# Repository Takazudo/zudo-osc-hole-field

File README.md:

# zudo-osc-hole-field

A standalone, cable-patched analog synthesizer on one flat 318 × 298 mm front panel, with 180 jacks above 144 controls and 33 module instances. Documentation domain: [zudo-osc-hole-field.zudolab.dev](https://zudo-osc-hole-field.zudolab.dev).

**Status:** pre-release design; no fabrication release exists.

The site is built with [zudo-circuit-doc](https://github.com/Takazudo/zudo-circuit-doc) on top of [zudo-doc](https://github.com/zudolab/zudo-doc). Authored project documentation lives under `doc/src/content/docs/`; exact-component evidence lives under `.claude/skills/`, and the component pages are generated from that evidence.

GitHub Actions runs the evidence validation, documentation checks, site build and built-site checks, plus Python unit tests under `scripts/` and `design/`, for pull requests and pushes to `main`. CI also replays aggregate source regeneration, including pinned native schematic and display checks, and retains any generated diff when that replay fails. These checks need no secrets and do not deploy the site; they do not establish electrical or physical qualification.

## Commands

| Command | What it does |
| --- | --- |
| `pnpm install` | Install dependencies |
| `pnpm dev` | Dev server, regenerating component pages as evidence changes |
| `pnpm build` | Publish selected models, generate component pages, build the site |
| `pnpm check` | Validate evidence, check generated output is current, type-check the site |
| `pnpm check:site` | Post-build checks: references, publication scope, links |
| `pnpm circuit:check` | Validate the component evidence (offline) |
| `pnpm circuit:generate` | Regenerate the component pages and the preflight report |
| `pnpm circuit:doctor` | Report required and optional tools |
| `pnpm previews:generate` | Render footprint previews (optional; needs Docker) |

Agent-facing commands (new component bundles, online source refresh) are listed in [circuit/WORKFLOW.md](circuit/WORKFLOW.md).

## Tool requirements

| Tool | Required | Used for |
| --- | --- | --- |
| Node.js 24 LTS (`>=24 <25`) | Yes | Everything |
| pnpm 11 (via corepack) | Yes | Install and scripts |
| Python ≥3.10 | Yes | Evidence validation (standard library only) |
| git | Yes | History and review diffs |
| Docker with the pinned KiCad image | No | Footprint previews |
| Chrome | No | Browser smoke check |
| Network | No | Downloading sources and assets only; the build is offline |
| easyeda2kicad | No | Importing CAD assets for LCSC-listed parts |

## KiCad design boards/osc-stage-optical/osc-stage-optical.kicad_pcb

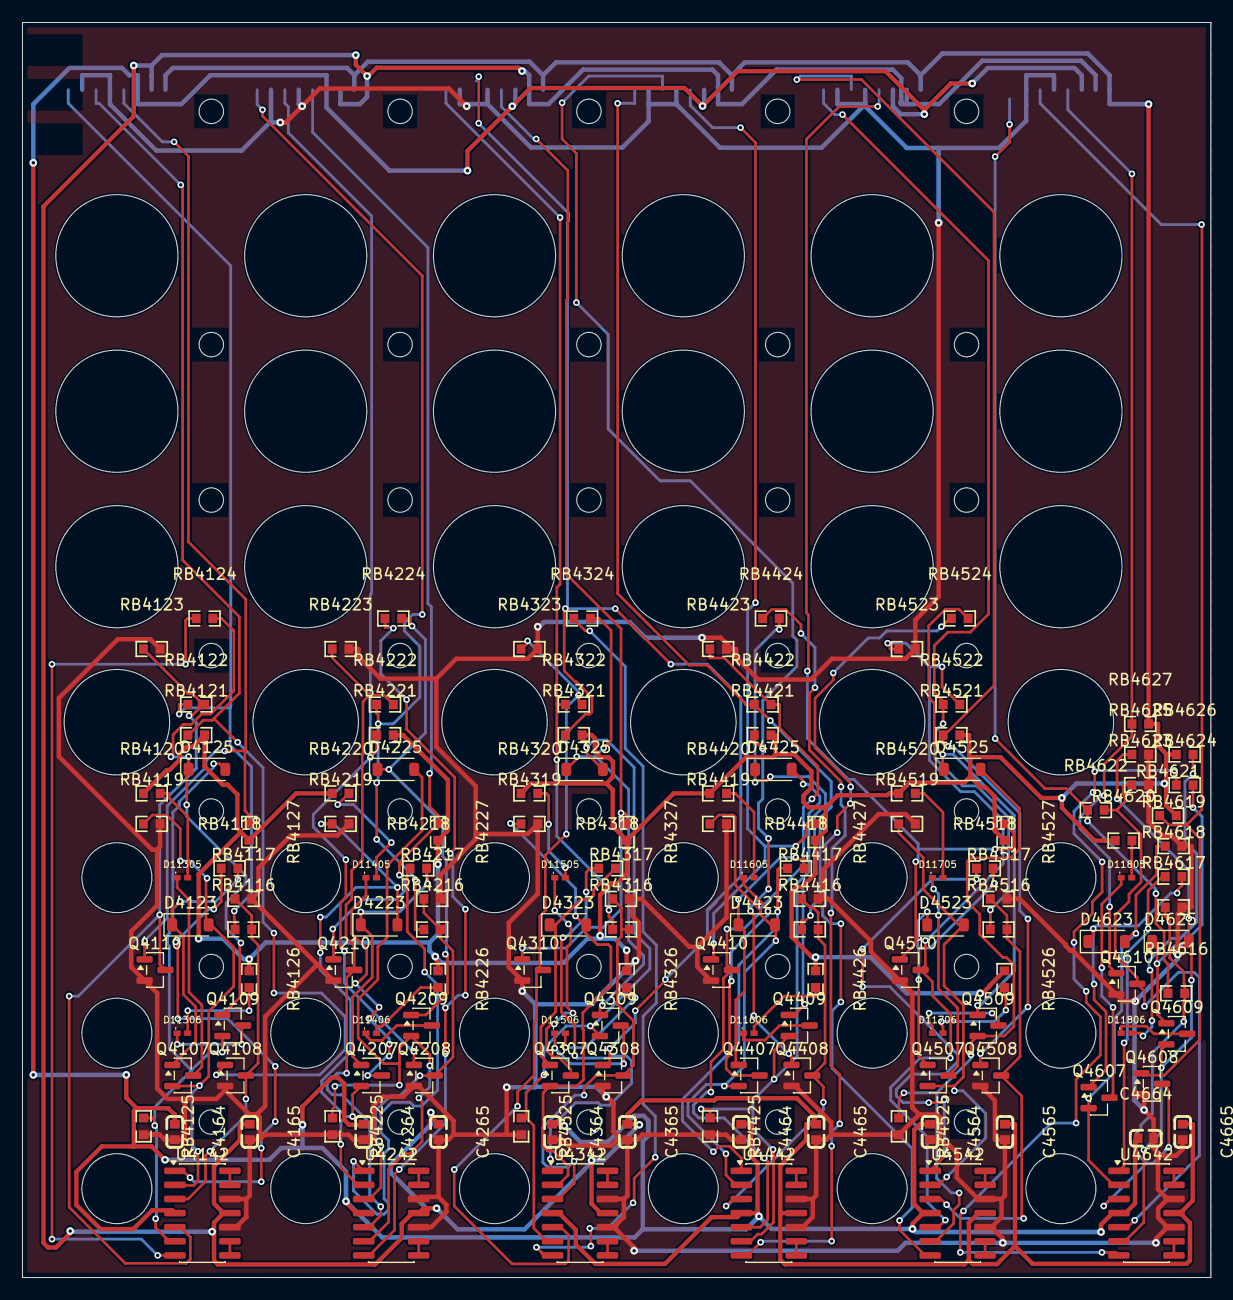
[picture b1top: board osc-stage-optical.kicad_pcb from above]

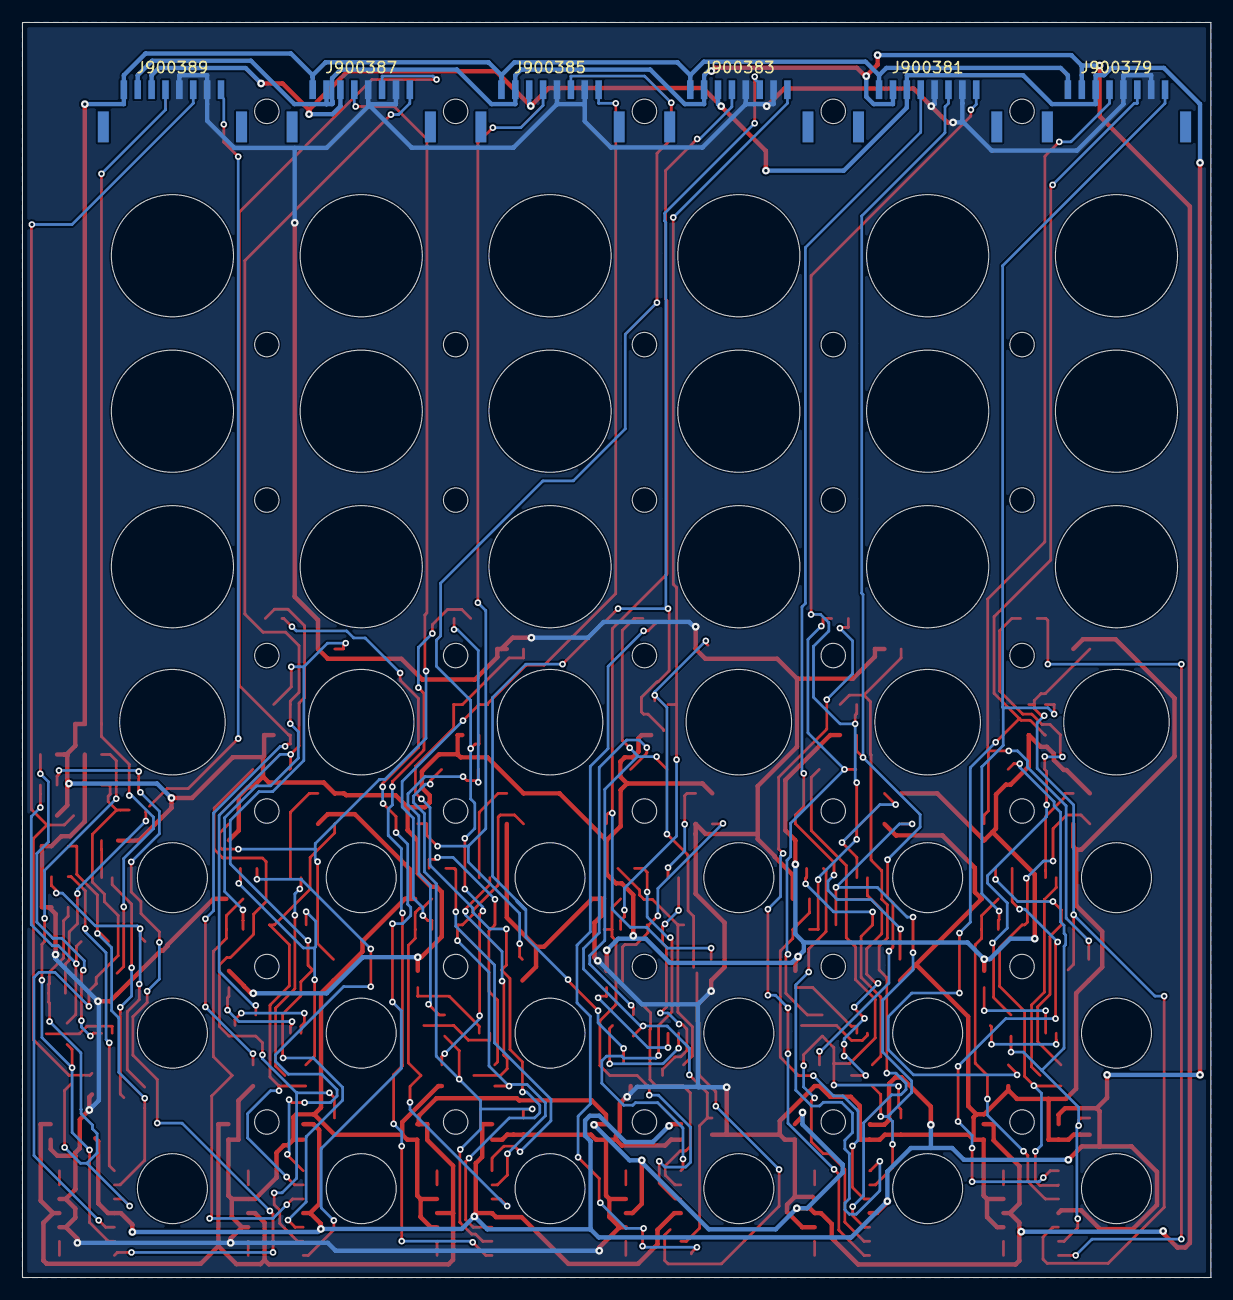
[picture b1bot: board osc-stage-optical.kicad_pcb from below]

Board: 2 copper layers, 107.0 x 113.0 mm, 221 parts (6 on the bottom side), 106 nets.

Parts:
C4164, C4165, C4264, C4265, C4364, C4365, C4464, C4465, C4564, C4565, C4664, C4665: 100 nF; C0603
D4123, D4125, D4223, D4225, D4323, D4325, D4423, D4425, D4523, D4525, D4623, D4625: BAS16GW-QX; SOD-123
D11305, D11306, D11405, D11406, D11505, D11506, D11605, D11606, D11705, D11706, D11805, D11806: APHHS1005QWF/D; LED0402-Kingbright-White
J900379, J900381, J900383, J900385, J900387, J900389: BM08B-GHS-TBT(LF)(SN); JST_GH8_BM_TopEntry
MH_EL-OPT-1, MH_EL-OPT-2, MH_EL-OPT-3, MH_EL-OPT-4, MH_EL-OPT-5, MH_EL-OPT-6, MH_EL-OPT-7, MH_EL-OPT-8, MH_EL-OPT-9, MH_EL-OPT-10, MH_EL-OPT-11, MH_EL-OPT-12, MH_EL-OPT-13, MH_EL-OPT-14, MH_EL-OPT-15, MH_EL-OPT-16, MH_EL-OPT-17, MH_EL-OPT-18, MH_EL-OPT-19, MH_EL-OPT-20, MH_EL-OPT-21, MH_EL-OPT-22, MH_EL-OPT-23, MH_EL-OPT-24, MH_EL-OPT-25, MH_EL-OPT-26, MH_EL-OPT-27, MH_EL-OPT-28, MH_EL-OPT-29, MH_EL-OPT-30, MH_EL-OPT-31, MH_EL-OPT-32, MH_EL-OPT-33, MH_EL-OPT-34, MH_EL-OPT-35: NPTH mounting hole
MH_EL-PASSAGE-1, MH_EL-PASSAGE-2, MH_EL-PASSAGE-3, MH_EL-PASSAGE-4, MH_EL-PASSAGE-5, MH_EL-PASSAGE-6, MH_EL-PASSAGE-7, MH_EL-PASSAGE-8, MH_EL-PASSAGE-9, MH_EL-PASSAGE-10, MH_EL-PASSAGE-11, MH_EL-PASSAGE-12, MH_EL-PASSAGE-13, MH_EL-PASSAGE-14, MH_EL-PASSAGE-15, MH_EL-PASSAGE-16, MH_EL-PASSAGE-17, MH_EL-PASSAGE-18, MH_EL-PASSAGE-19, MH_EL-PASSAGE-20, MH_EL-PASSAGE-21, MH_EL-PASSAGE-22, MH_EL-PASSAGE-23, MH_EL-PASSAGE-24, MH_EL-PASSAGE-25, MH_EL-PASSAGE-26, MH_EL-PASSAGE-27, MH_EL-PASSAGE-28, MH_EL-PASSAGE-29, MH_EL-PASSAGE-30, MH_EL-PASSAGE-31, MH_EL-PASSAGE-32, MH_EL-PASSAGE-33, MH_EL-PASSAGE-34, MH_EL-PASSAGE-35, MH_EL-PASSAGE-36, MH_EL-PASSAGE-37, MH_EL-PASSAGE-38, MH_EL-PASSAGE-39, MH_EL-PASSAGE-40, MH_EL-PASSAGE-41, MH_EL-PASSAGE-42: NPTH mounting hole
Q4107, Q4109, Q4207, Q4209, Q4307, Q4309, Q4407, Q4409, Q4507, Q4509, Q4607, Q4609: MMBT3904,215; SOT-23
Q4108, Q4110, Q4208, Q4210, Q4308, Q4310, Q4408, Q4410, Q4508, Q4510, Q4608, Q4610: 2N7002,215; SOT-23
RB4116, RB4122, RB4216, RB4222, RB4316, RB4322, RB4416, RB4422, RB4516, RB4522, RB4616, RB4622: 150000 Ω; R0603
RB4117, RB4118, RB4123, RB4124, RB4217, RB4218, RB4223, RB4224, RB4317, RB4318, RB4323, RB4324, RB4417, RB4418, RB4423, RB4424, RB4517, RB4518, RB4523, RB4524, RB4617, RB4618, RB4623, RB4624: 10000 Ω; R0603
RB4119, RB4125, RB4219, RB4225, RB4319, RB4325, RB4419, RB4425, RB4519, RB4525, RB4619, RB4625: 1000 Ω; R0603
RB4120, RB4126, RB4220, RB4226, RB4320, RB4326, RB4420, RB4426, RB4520, RB4526, RB4620, RB4626: 1200 Ω; R0603
RB4121, RB4127, RB4221, RB4227, RB4321, RB4327, RB4421, RB4427, RB4521, RB4527, RB4621, RB4627: 100000 Ω; R0603
U4142, U4242, U4342, U4442, U4542, U4642: OPA4196IDR; SOIC-14_3.9x8.7mm_P1.27mm

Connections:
+5V: J900379.8, J900381.8, J900383.8, J900385.8, J900387.8, J900389.8, RB4120.1, RB4121.2, RB4126.1, RB4127.2, RB4220.1, RB4221.2, RB4226.1, RB4227.2, RB4320.1, RB4321.2, RB4326.1, RB4327.2, RB4420.1, RB4421.2, RB4426.1, RB4427.2, RB4520.1, RB4521.2, RB4526.1, RB4527.2, RB4620.1, RB4621.2, RB4626.1, RB4627.2
+12V: C4164.1, C4264.1, C4364.1, C4464.1, C4564.1, C4664.1, J900379.6, J900381.6, J900383.6, J900385.6, J900387.6, J900389.6, U4142.4, U4242.4, U4342.4, U4442.4, U4542.4, U4642.4
-12V: C4165.1, C4265.1, C4365.1, C4465.1, C4565.1, C4665.1, J900379.7, J900381.7, J900383.7, J900385.7, J900387.7, J900389.7, U4142.11, U4242.11, U4342.11, U4442.11, U4542.11, U4642.11
AGND: C4164.2, C4165.2, C4264.2, C4265.2, C4364.2, C4365.2, C4464.2, C4465.2, C4564.2, C4565.2, C4664.2, C4665.2, J900379.2, J900379.4, J900381.2, J900381.4, J900383.2, J900383.4, J900385.2, J900385.4, J900387.2, J900387.4, J900389.2, J900389.4, Q4108.2, Q4110.2, Q4208.2, Q4210.2, Q4308.2, Q4310.2, Q4408.2, Q4410.2, Q4508.2, Q4510.2, Q4608.2, Q4610.2, RB4117.2, RB4119.2, RB4123.2, RB4125.2, RB4217.2, RB4219.2, RB4223.2, RB4225.2, RB4317.2, RB4319.2, RB4323.2, RB4325.2, RB4417.2, RB4419.2, RB4423.2, RB4425.2, RB4517.2, RB4519.2, RB4523.2, RB4525.2, RB4617.2, RB4619.2, RB4623.2, RB4625.2, U4142.10, U4142.12, U4242.10, U4242.12, U4342.10, U4342.12, U4442.10, U4442.12, U4542.10, U4542.12, U4642.10, U4642.12
X00BF5622D64D21A15AC7: J900389.3, Q4608.1, RB4621.1
X1AC60263070127D75110: D4225.1, Q4209.1, RB4224.2
X1BBA3C5B996B98DC88F4: J900383.5, Q4310.1, RB4327.1
X1D82190ED747CF04DE0E: RB4624.1, U4642.7
X1DC1CF348CA9F3663A68: Q4410.3, RB4422.2, RB4423.1, U4442.5
X1E1A841AE6BDBA6F12FD: D4423.1, Q4407.1, RB4418.2
X1E3069D9C725A8540F2B: Q4210.3, RB4222.2, RB4223.1, U4242.5
X1FFAABFEE1FB66BF068E: D4325.2, Q4309.2, RB4325.1, U4342.6
X2AC9B8A8C44204D4DCFE: D4423.2, Q4407.2, RB4419.1, U4442.2
X2E5349539AD45B40EC09: D4125.1, Q4109.1, RB4124.2
X4B6E43806072E34C24A9: D11505.2, RB4320.2
X5EF5AA803DEECA814BD8: D11605.2, RB4420.2
X6A8CD0115BB6A0D0366E: D11706.1, Q4509.3
X6A51B6341523E19D8CF4: D11806.1, Q4609.3
X6B20A2AEE7A32617CD3E: D11405.1, Q4207.3
X6C1DA0497CB43057E117: Q4608.3, RB4616.2, RB4617.1, U4642.3
X6E9F88B4B3BE457C0226: U4342.13, U4342.14
X7E65864BB7CF7411DC10: U4442.13, U4442.14
X8A939B676B6F87E5F9A3: J900383.1, RB4316.1, RB4322.1
X8ECADF7A8E0F09B77152: D11305.2, RB4120.2
X9A280F085D66F529A415: D11706.2, RB4526.2
X9B81034A8BEE6B2EBDA4: J900385.3, Q4408.1, RB4421.1
X9C2EA2BC9623A3E6139C: D11606.2, RB4426.2
X9E4D82CA4412C9189909: Q4508.3, RB4516.2, RB4517.1, U4542.3
X9E76C286BAE34857728C: D4323.2, Q4307.2, RB4319.1, U4342.2
X9F3B44E9C4F1B46F49CF: RB4124.1, U4142.7
X9F61A7055EEEA35F62E7: J900389.1, RB4616.1, RB4622.1
X10C845ED7B7C5BB89B7C: RB4224.1, U4242.7
X47BB1FB0495EA911FAB2: D4325.1, Q4309.1, RB4324.2
X61E1C31F3ACE5341D7D3: Q4408.3, RB4416.2, RB4417.1, U4442.3
X71B9E05195347FA9C8C2: J900387.1, RB4516.1, RB4522.1
X87EB8972925CDC4B1D2E: J900381.3, Q4208.1, RB4221.1
X88DA5861B6BCC3B653DE: D11606.1, Q4409.3
X95E38523BB35DF833AE9: J900385.1, RB4416.1, RB4422.1
X131A163062BE66F69054: J900385.5, Q4410.1, RB4427.1
X244B291CBC2C7076AA07: D11605.1, Q4407.3
X419B40DA0975D322AD5F: D11405.2, RB4220.2
X498F1E66A5FADE06B7E4: Q4308.3, RB4316.2, RB4317.1, U4342.3
X688ECBAA39258DC2D00D: D11805.2, RB4620.2
X789C67863FBCE430DA0E: RB4518.1, U4542.1
X799DB867A3031F5AB77F: RB4618.1, U4642.1
X853F40255E51475DF7A1: D4523.2, Q4507.2, RB4519.1, U4542.2
X867ABDC689D5BFF10061: Q4110.3, RB4122.2, RB4123.1, U4142.5
X2504E7ECC0354FA168E7: D4223.2, Q4207.2, RB4219.1, U4242.2
X3295DB827CE8AAE574FD: RB4324.1, U4342.7
X3439E778D35CDF6DFDF1: Q4108.3, RB4116.2, RB4117.1, U4142.3
X04963B7F211123194254: RB4318.1, U4342.1
X7307E027BF83453C3524: D11705.2, RB4520.2
X9141FD25BB2109174A88: U4442.8, U4442.9
X9858BBCA9970C9FCB86B: RB4524.1, U4542.7
X10852B4E217E1D395843: J900381.1, RB4216.1, RB4222.1
X25962DC0D080647130A4: U4542.13, U4542.14
X43904EB1FC7EDB0AA335: D11406.2, RB4226.2
X61003EE13806AD930803: J900387.5, Q4510.1, RB4527.1
X63613ECE89F282A509B6: J900383.3, Q4308.1, RB4321.1
X138812A99E0187B8D67A: D4625.2, Q4609.2, RB4625.1, U4642.6
X332730C2FDDA08CAED83: D4125.2, Q4109.2, RB4125.1, U4142.6
X634047C9CD5843892462: U4342.8, U4342.9
X4422711AFCCDBA718D4A: D4525.1, Q4509.1, RB4524.2
X53746081A37DAC301ADD: D11705.1, Q4507.3
X797009172D71EAFEBB1A: U4142.13, U4142.14
XA9DE434B9AA0F8C536DE: D11406.1, Q4209.3
XA68EA9E2F5379B7D8F08: D11305.1, Q4107.3
XAA0301884F69AD0E7337: J900379.5, Q4110.1, RB4127.1
XADBE90B291D159BD3BB1: D4523.1, Q4507.1, RB4518.2
XB2EBA66DAA21CB8551C8: RB4424.1, U4442.7
XB3B9A2AF2F7FA0D340E0: U4642.8, U4642.9
XB7B603420FD77620332F: D4425.1, Q4409.1, RB4424.2
XB7C2F315B2A72C7196F7: J900379.1, RB4116.1, RB4122.1
XB8D83C764066FEA571D7: J900381.5, Q4210.1, RB4227.1
XB9F0BC4557B5B5EF0AEC: Q4310.3, RB4322.2, RB4323.1, U4342.5
XB9FF60B0A66F70D425BE: D11805.1, Q4607.3
XB42EEE9219CFC7A853BD: D4323.1, Q4307.1, RB4318.2
XB899437C2EA9066F92F1: D4623.1, Q4607.1, RB4618.2
XBE667D2100526CFBC980: Q4510.3, RB4522.2, RB4523.1, U4542.5
XBED0A5748F4252A15663: D11306.2, RB4126.2
XC63C4BF13BA35D8AB361: D11806.2, RB4626.2
XCBB338FD60809F1C4554: U4242.13, U4242.14
XCF0902D8596AED7F7C86: D11505.1, Q4307.3
XCF44320172AB28A8C69A: U4642.13, U4642.14
XD5D1FFC8551A1CE41366: RB4418.1, U4442.1
XDCA4AB4D7D77D8669D15: Q4610.3, RB4622.2, RB4623.1, U4642.5
XDFCEC6E90F901E5E001F: D11506.2, RB4326.2
XE0FCBC3BB1F0803DF2AA: RB4218.1, U4242.1
XE1BE3DF4F60D2EE008D3: U4242.8, U4242.9
XE56B22348305C8B48C30: D4225.2, Q4209.2, RB4225.1, U4242.6
XE88A58D060DEC4E258C1: D4623.2, Q4607.2, RB4619.1, U4642.2
XE5206E58490CA0C0DF9B: D11506.1, Q4309.3
XE81531DE199582BE1344: J900389.5, Q4610.1, RB4627.1
XE1168244D1DE58C973DA: J900387.3, Q4508.1, RB4521.1
XEBD613C7EBC4FC656B12: D4223.1, Q4207.1, RB4218.2
XEE002239713F1E6CFAB6: D4123.1, Q4107.1, RB4118.2
XEEC69D3919A8A746094D: U4142.8, U4142.9
XEEFC9E5D4F8B5267F230: D4425.2, Q4409.2, RB4425.1, U4442.6
XF03AEC4C984C52D7EB57: D4525.2, Q4509.2, RB4525.1, U4542.6
XF5E48AE779812F227AE3: D4625.1, Q4609.1, RB4624.2
XF14FD29BB5FDF6626F7F: U4542.8, U4542.9
XF217E605C28C4AFFF4AE: D11306.1, Q4109.3
XFB651FD5AA7E9ACFDC9E: Q4208.3, RB4216.2, RB4217.1, U4242.3
XFC4750185D5F3794B5AF: D4123.2, Q4107.2, RB4119.1, U4142.2
XFD5706614908F1E1329B: J900379.3, Q4108.1, RB4121.1
XFF1B5FFC9904605776EA: RB4118.1, U4142.1

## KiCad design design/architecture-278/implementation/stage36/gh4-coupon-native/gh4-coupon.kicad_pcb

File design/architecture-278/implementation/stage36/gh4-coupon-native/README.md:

# GH4 native coupon — REVIEW ONLY

Isolated unpowered evaluation coupon, authored on x0x on 2026-10-18 from
`23b0652fdc981b374c7d5c6b053e509372b008b0`. This directory alone is new.
Canonical A01 boards, historical stages, both viewers and parent PR #286 are unchanged.
No manufacturing release, upload, supplier contact, order or physical success is claimed.

## Native result

- KiCad CLI and pcbnew: **10.0.6**, existing Ubuntu WSL Docker image
  `kicad/kicad@sha256:18693567392b80da435f9fa952ce3a3e534c66eb5a6033f5b9c80aa3b19dd3ec`.
- `erc.rpt`: zero errors and warnings.
- `drc.rpt`: zero DRC violations, zero unconnected pads, zero schematic parity issues.
- `review-only/audit.json`: exported netlist, pin correspondence, placement, drill and
  Gerber checks. `review-only/gerber-review.png` renders actual exported Gerber
  linear strokes and flashed apertures. This limited parser rejects arcs/regions;
  it is not a substitute for a fabricator CAM review.
- `review-only/board-top.pdf`, `.png` and `.svg`: native KiCad board renderings.
- `REVIEW.md`: independent review and source/native bindings.

Native hashes are recorded in `review-only/audit.json`; `SHA256SUMS.txt` binds the
retained deliverables. KiCad creates new object UUIDs on regeneration; later
regeneration requires fresh native checks, exports, hashes and review.

## Exact identity and construction

J1 is JST **BM04B-GHS-TBT(LF)(SN)**, top-entry GH4, supplier identity **C161692**.
One populated header per board. The pinned maintained footprint is a library
asset, not a vendor-certified footprint. Source and SHA256 are in the unchanged
`../gh4-coupon-plan/design.json`; attribution/license are retained in
`FOOTPRINT-LICENSE.md`. The upstream footprint is byte-identical to pinned revision
`f8a45b4665c28a6280e46eefe9fd4df81d2cd17b`.

Manufacturer basis: JST eGH catalog, printed pages 2–3, retained in
`design/connectors/sources/jst-gh.pdf`, SHA256
`b1dcb317b6b9a4fbbedd2dbf42c64c95306a252d23de8933b85fcf161240b722`.
The mounting-surface view rotates 180 degrees without mirroring into this top
component view: signal pin 1 left, signal row below the body, mechanical lands
above. Exact six land centers/sizes match the reviewed design. No 3D body or
physical fit verification is inferred.

Overall 80×100 mm, functional 80×80 mm, two 10 mm rails. Four F.Cu-only independent
0.25 mm nets GH1–GH4 connect J1.n to TPn. No supply or planes. MP lands have no
signal net. Both-face clamp reservations and 1 mm V-cut bands are native rule
areas; 1 mm outer copper clearance and 0.25 mm spacing/track width are enforced.
Three Ø1 copper/Ø2 mask fiducials; three Ø2 NPTH tooling holes; four Ø2 testpads.
Only J1 has paste: four signal and two MP apertures. Testpads/fiducials/tooling
are excluded from assembly BOM/CPL. Bare lands have no component courtyard;
`missing_courtyard` is explicitly ignored, and all other ignored native defaults
are enumerated in the DRC report. J1 retains its pinned courtyard.

## Export conventions and unreleased status

All manufacturing-style files live in **review-only/** and are not order files.
The perimeter is four Edge.Cuts segments. Full-width V-cuts at y10/y90 are
annotations on `Dwgs.User`, named `V-CUT-REVIEW`; they are not slots. That Gerber
also carries explanatory text; eventual fabrication interpretation must explicitly
identify the two score lines. There is no automatic V-score machining instruction.

`placement-native.csv` contains only J1, mm, top, 0 degrees, X40 Y−50. KiCad's
absolute placement export uses Y up; design/PCB coordinates use Y down from the
upper-left overall origin. Therefore Y−50 corresponds to design y50. This is a
native review CPL, not a supplier-normalized upload. Do not reinterpret it without
an explicit transform and placement preview. `bom-review-only.csv` contains one
exact header per board, not a five-board order quantity.

## Commands and evidence

Run from repository root with the existing pinned image; do not run regen-all:

```sh
n=design/architecture-278/implementation/stage36/gh4-coupon-native
bash scripts/kicad/run.sh kicad-cli version
bash scripts/kicad/run.sh python3 "$n/generate.py"
bash scripts/kicad/run.sh kicad-cli sch erc --exit-code-violations --output "$n/erc.rpt" "$n/gh4-coupon.kicad_sch"
bash scripts/kicad/run.sh kicad-cli pcb drc --schematic-parity --exit-code-violations --output "$n/drc.rpt" "$n/gh4-coupon.kicad_pcb"
bash "$n/export-review.sh"
python3 "$n/audit_review.py"  # needs already-installed Pillow
```

`export-review.sh` records the exact native netlist/SVG/Gerber/drill/placement
commands. Native PDF command used:
`bash scripts/kicad/run.sh kicad-cli pcb export pdf --layers F.Cu,F.Silkscreen,Edge.Cuts,Dwgs.User --output "$n/review-only/board-top.pdf" "$n/gh4-coupon.kicad_pcb"`.
PDF rasterization used existing Windows Python 3.12.14, pypdfium2 5.14.0 at scale5,
cropped to (0,0,1150,1450); Gerber rendering used Pillow 12.3.0.

Before and after native authoring, the existing Node 22.22.2 installation ran
`node node_modules/@takazudo/zudo-circuit-doc/bin/zudo-circuit-doc.js validate`:
PASS. SCOPE: manual inventory, 68 lines, zero declared placements unverified,
no schematic/placement binding; pin-asset check performed. The final direct CLI
`check` passed generated-page/preflight/model checks and all 31 committed footprint
previews. Three `gh4-coupon-plan/test_design.py` source tests passed. Full pnpm
workspace TypeScript/site checks and whole OSC regeneration were NOT RUN; unrelated
site/native inputs were not edited. No browser-viewer test was rerun.

## Failures retained and corrected

1. Sandboxed WSL enumeration returned E_ACCESSDENIED; approved read-only host
   execution succeeded. Windows PATH/standard installation registry contained no
   KiCad; WSL had no standalone KiCad package/binary. Existing pinned Docker image
   returned exact 10.0.6. No KiCad install, image pull, default or daemon change.
2. First direct validation command guessed `bin/cli.mjs` and failed MODULE_NOT_FOUND.
   The actual entrypoint is `bin/zudo-circuit-doc.js`.
3. `pnpm circuit:check` attempted automatic dependency reconciliation and aborted
   with ERR_PNPM_ABORTED_REMOVE_MODULES_DIR_NO_TTY before replacing modules. Its log
   referenced pnpm 11.5.2 temporary tool cache. No install was intentionally run;
   switched to the existing direct CLI to avoid automatic package-manager work.
4. Windows footprint download hit sandbox WinError10013; WSL public download
   succeeded, required SHA256 matched. No credentials were needed.
5. Initial pcbnew API calls failed for LSET constructors/union and the obsolete
   SetDoNotAllowCopperPour method. Replaced with AddLayer and SetDoNotAllowZoneFills.
   Initial board DRC attempt could not open the not-yet-generated board.
6. First schematic load failed with a literal multiline string; escaped it.
   `erc-02.rpt` retains 23 warnings (off-grid schematic coordinates and absent
   project/library discovery during incomplete generation). Corrected schematic
   grid coordinates and completed local project/library files; final ERC zero.
7. Independent review found local /GHn vs PCB GHn naming. Changed to global GHn
   labels. `drc-parity-first.rpt` then retained 11 metadata parity warnings:
   datasheet field, TP values, and six board-only features. Corrected fields and
   explicit board-only attributes; final parity zero. `drc-first.rpt` retains the
   earlier clean geometry-only check, not final parity evidence.
8. The auxiliary audit initially assumed the old numeric/net-name PCB syntax;
   KiCad 10 stores direct net names. Corrected the reader; final audit passed.
9. Staged whitespace checking identified raw KiCad SVG trailing spaces and
   Windows receipt CRLF. Narrow local attributes preserve reviewed SVG bytes and
   accept CRLF only for audit.json/BOM; authored files remain checked. The hash
   manifest uses LF. The initial pathspec staging matched no files; an explicit
   file list was used, excluding `.kicad_prl` and Python caches.

## Handoff boundary

Remote PR #287 branch `agent/278-stage28-din-harness-20261017` was read at pinned
`23b0652fdc981b374c7d5c6b053e509372b008b0` before any coupon write. Work used an
independent no-hardlinks clone under this task workspace, never another session's
worktree. Before pushing, the parent must re-confirm current remote head and the
push route. The clone's origin still points to the read-only source checkout;
do not push to that local origin. No push was made.

Physical soldering, continuity/isolation measurements, grip/latch/access, board
bow, flex/durability and assembly-process qualification are NOT RUN. Supplier
placement preview, V-score interpretation and release approval remain later
manufacturing gates. Native rule checks do not establish those physical results.

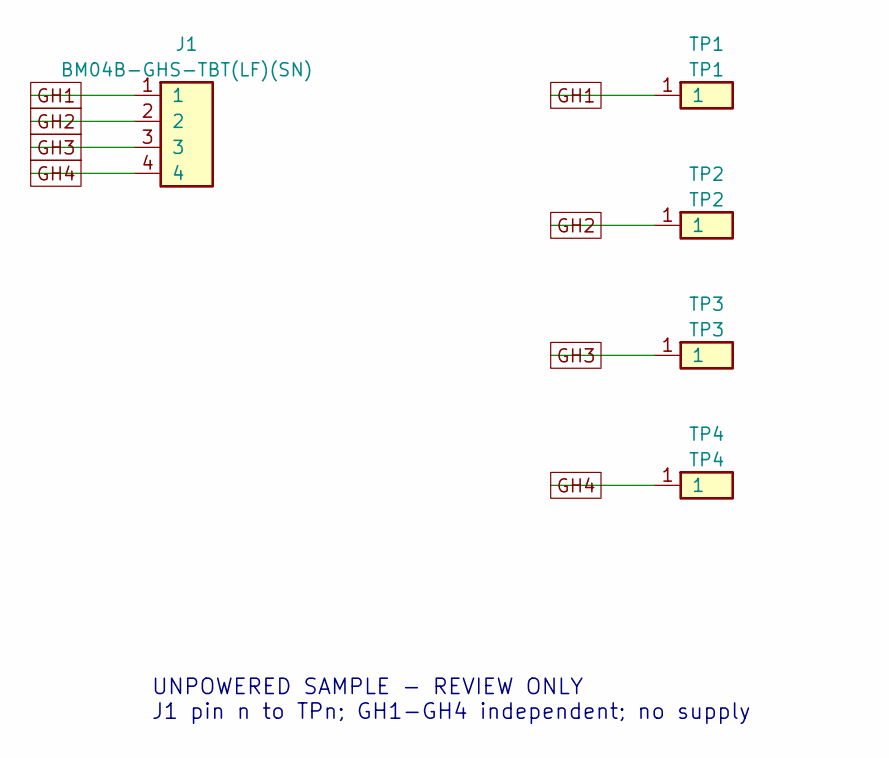
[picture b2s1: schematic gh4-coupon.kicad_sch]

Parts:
J1: BM04B-GHS-TBT(LF)(SN); JST_GH_BM04B-GHS-TBT_1x04-1MP_P1.25mm_Vertical
TP1: TP1; Coupon_TP_2mm
TP2: TP2; Coupon_TP_2mm
TP3: TP3; Coupon_TP_2mm
TP4: TP4; Coupon_TP_2mm

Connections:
GH1: J1.1, TP1.1
GH2: J1.2, TP2.1
GH3: J1.3, TP3.1
GH4: J1.4, TP4.1

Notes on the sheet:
UNPOWERED SAMPLE - REVIEW ONLY J1 pin n to TPn; GH1-GH4 independent; no supply

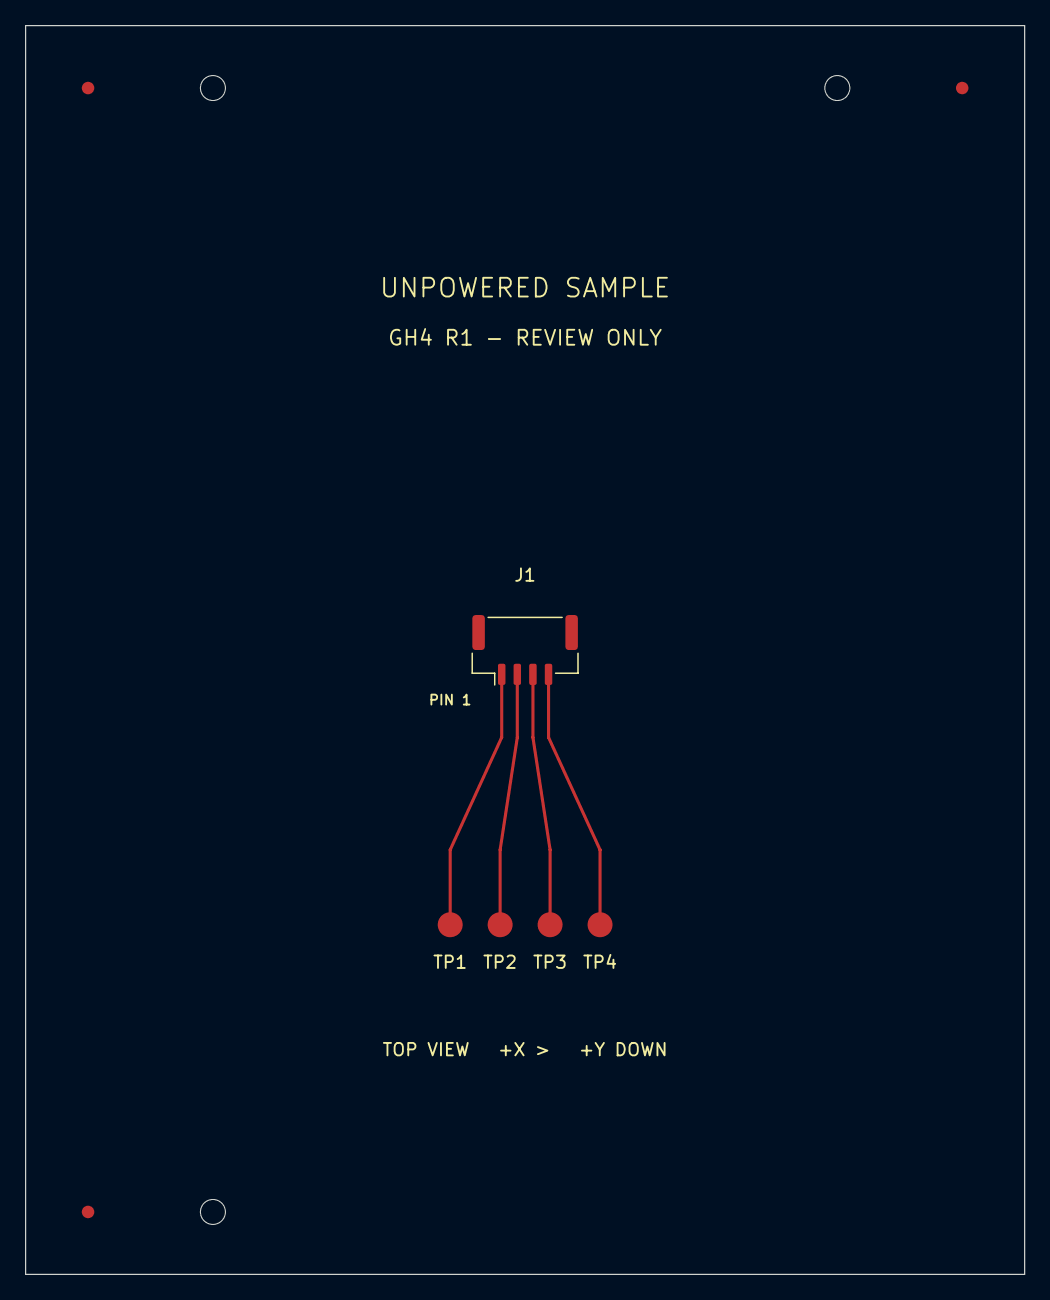
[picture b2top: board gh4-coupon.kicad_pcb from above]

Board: 2 copper layers, 80.0 x 100.0 mm, 11 parts (0 on the bottom side), 4 nets.

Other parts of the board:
FID1, FID2, FID3: Coupon_Fiducial_1mm
H1, H2, H3: Coupon_Tooling_2mm

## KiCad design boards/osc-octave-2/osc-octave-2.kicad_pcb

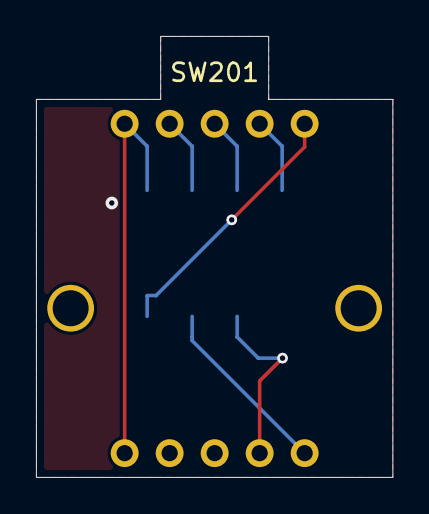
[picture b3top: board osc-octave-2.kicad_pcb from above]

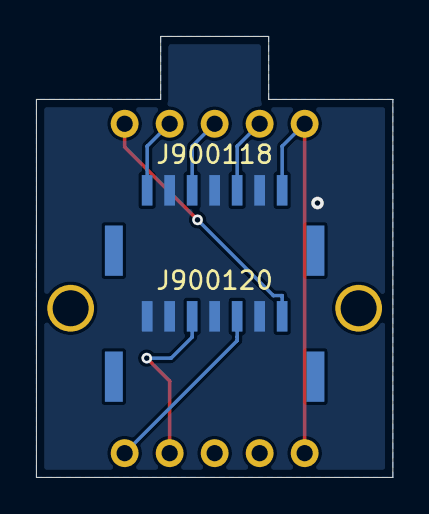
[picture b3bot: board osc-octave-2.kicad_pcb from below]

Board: 2 copper layers, 19.8 x 24.5 mm, 3 parts (2 on the bottom side), 8 nets.

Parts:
J900118, J900120: BM07B-GHS-TBT(LF)(SN); JST_GH7_BM_TopEntry
SW201: SRBV160803

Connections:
AGND: J900118.2, J900118.4, J900118.6, J900120.2, J900120.4, J900120.6, J900120.7
X5CF52A5D3BDB84554948: J900118.3, SW201.2
X9CC58764476721DDB0F8: J900120.3, SW201.6
X56C3D53C39023A952E08: J900118.7, SW201.4
X64D220928EDA3905C0D6: J900118.1, SW201.1, SW201.10
XA9392E54A81C8E2987E0: J900118.5, SW201.3
XE979A9D83B4902B292ED: J900120.1, SW201.5
XFE31B748A31181E56A8B: J900120.5, SW201.7

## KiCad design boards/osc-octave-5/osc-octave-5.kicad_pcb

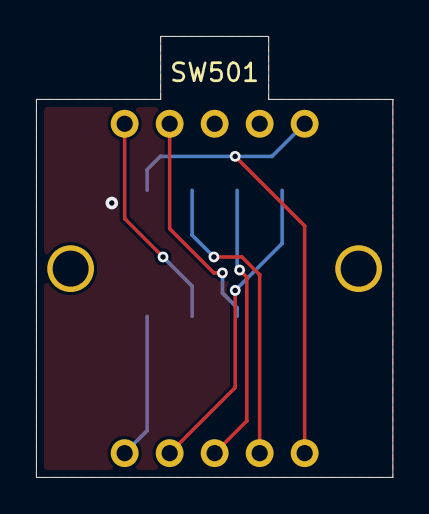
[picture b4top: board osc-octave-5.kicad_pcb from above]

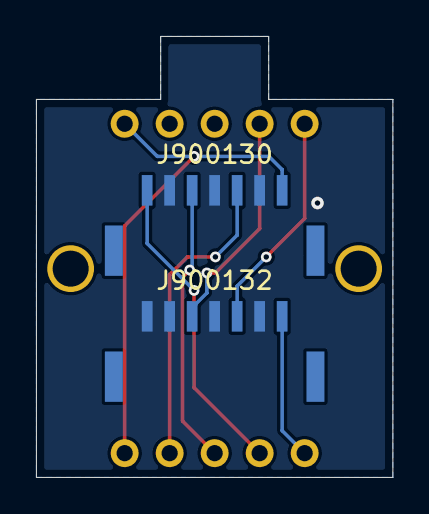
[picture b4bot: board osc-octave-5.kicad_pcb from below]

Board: 2 copper layers, 19.8 x 24.5 mm, 3 parts (2 on the bottom side), 8 nets.

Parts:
J900130, J900132: BM07B-GHS-TBT(LF)(SN); JST_GH7_BM_TopEntry
SW501: SRBV160803

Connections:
AGND: J900130.2, J900130.4, J900130.6, J900132.2, J900132.4, J900132.6, J900132.7
X5CF52A5D3BDB84554948: J900130.3, SW501.2
X9CC58764476721DDB0F8: J900132.3, SW501.6
X56C3D53C39023A952E08: J900130.7, SW501.4
X570616CB52B08D70FD0C: J900130.1, SW501.1, SW501.10
XA9392E54A81C8E2987E0: J900130.5, SW501.3
XE979A9D83B4902B292ED: J900132.1, SW501.5
XFE31B748A31181E56A8B: J900132.5, SW501.7

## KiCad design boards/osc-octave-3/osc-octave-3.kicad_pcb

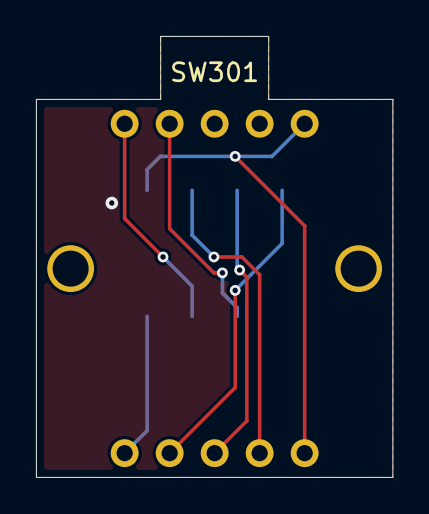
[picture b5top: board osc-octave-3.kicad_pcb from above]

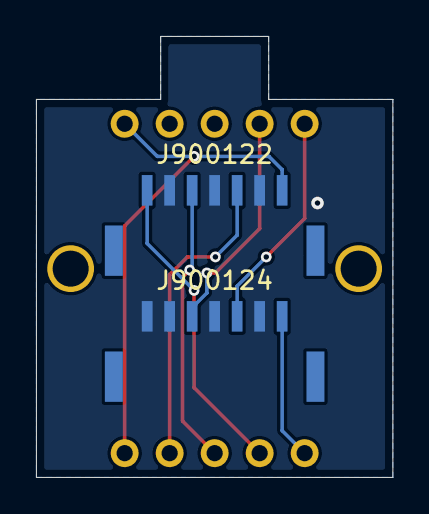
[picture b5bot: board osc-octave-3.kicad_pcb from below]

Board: 2 copper layers, 19.8 x 24.5 mm, 3 parts (2 on the bottom side), 8 nets.

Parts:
J900122, J900124: BM07B-GHS-TBT(LF)(SN); JST_GH7_BM_TopEntry
SW301: SRBV160803

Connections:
AGND: J900122.2, J900122.4, J900122.6, J900124.2, J900124.4, J900124.6, J900124.7
X5CF52A5D3BDB84554948: J900122.3, SW301.2
X5D31DD5D6E642F7542A9: J900122.1, SW301.1, SW301.10
X9CC58764476721DDB0F8: J900124.3, SW301.6
X56C3D53C39023A952E08: J900122.7, SW301.4
XA9392E54A81C8E2987E0: J900122.5, SW301.3
XE979A9D83B4902B292ED: J900124.1, SW301.5
XFE31B748A31181E56A8B: J900124.5, SW301.7

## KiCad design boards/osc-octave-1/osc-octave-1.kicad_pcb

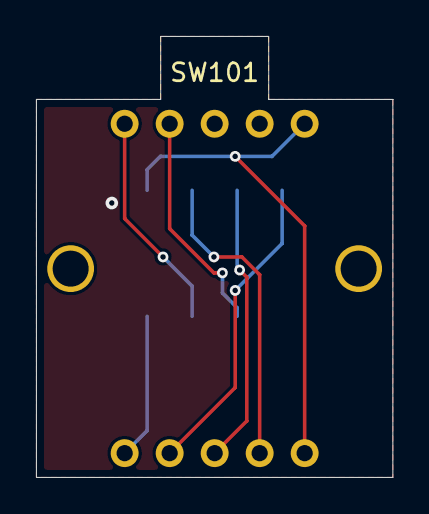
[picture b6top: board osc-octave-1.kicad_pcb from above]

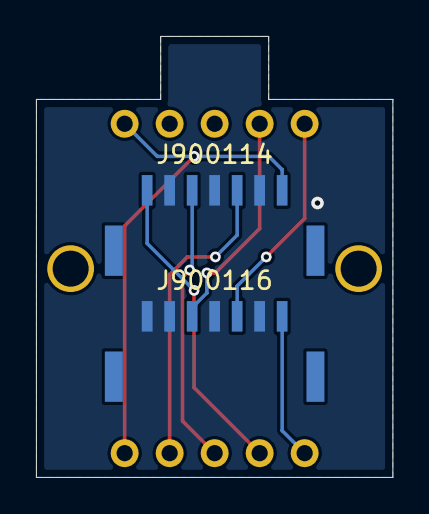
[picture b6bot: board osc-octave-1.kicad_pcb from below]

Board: 2 copper layers, 19.8 x 24.5 mm, 3 parts (2 on the bottom side), 8 nets.

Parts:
J900114, J900116: BM07B-GHS-TBT(LF)(SN); JST_GH7_BM_TopEntry
SW101: SRBV160803

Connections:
AGND: J900114.2, J900114.4, J900114.6, J900116.2, J900116.4, J900116.6, J900116.7
X5CF52A5D3BDB84554948: J900114.3, SW101.2
X9CC58764476721DDB0F8: J900116.3, SW101.6
X56C3D53C39023A952E08: J900114.7, SW101.4
X90EEDB72A75DC6F13F0D: J900114.1, SW101.1, SW101.10
XA9392E54A81C8E2987E0: J900114.5, SW101.3
XE979A9D83B4902B292ED: J900116.1, SW101.5
XFE31B748A31181E56A8B: J900116.5, SW101.7

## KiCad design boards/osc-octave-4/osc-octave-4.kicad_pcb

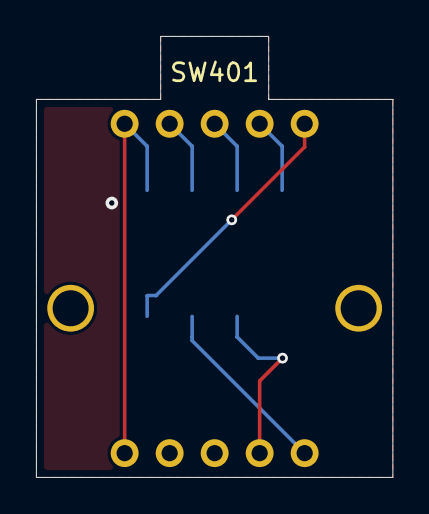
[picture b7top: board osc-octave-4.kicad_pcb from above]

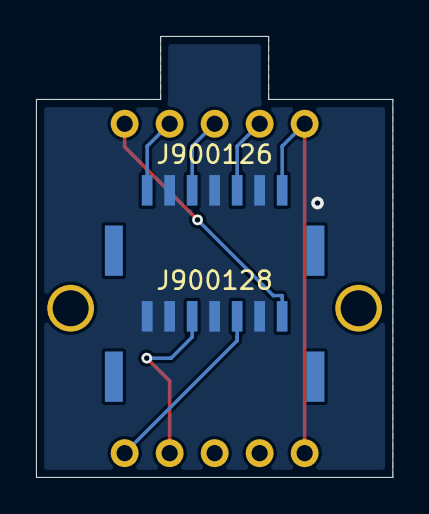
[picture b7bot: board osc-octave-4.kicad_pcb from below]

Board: 2 copper layers, 19.8 x 24.5 mm, 3 parts (2 on the bottom side), 8 nets.

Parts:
J900126, J900128: BM07B-GHS-TBT(LF)(SN); JST_GH7_BM_TopEntry
SW401: SRBV160803

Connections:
AGND: J900126.2, J900126.4, J900126.6, J900128.2, J900128.4, J900128.6, J900128.7
X5CF52A5D3BDB84554948: J900126.3, SW401.2
X9CC58764476721DDB0F8: J900128.3, SW401.6
X56C3D53C39023A952E08: J900126.7, SW401.4
X62232080C40C3946475B: J900126.1, SW401.1, SW401.10
XA9392E54A81C8E2987E0: J900126.5, SW401.3
XE979A9D83B4902B292ED: J900128.1, SW401.5
XFE31B748A31181E56A8B: J900128.5, SW401.7
